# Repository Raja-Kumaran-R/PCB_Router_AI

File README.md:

# KiCad Autorouter with A*

This project implements a simple autorouter for KiCad PCB files using the A* search algorithm.  
It parses `.kicad_pcb` files, generates routes, and injects them back into the PCB design.

## Features
- Parse PCB layout files to extract pads, nets, and obstacles.
- Route nets automatically using A* algorithm.
- Support for via creation between layers.
- Generates new routed KiCad PCB file.

## Current Progress
1. Many sample PCB files are included:
2. Next step: extend support for **4-layer PCBs** and implementing LLM.

## Usage

### Step 1: Parse the PCB File
```bash
python parser.py <file_name>.kicad_pcb
```
This will generate an `input.json` file containing the parsed layout information.

### Step 2: Run A* Routing
```bash
python astar.py input.json > output.json
```
This creates an `output.json` file containing the generated routing paths.

### Step 3: Inject Routes into PCB
```bash
python inject_routes.py output.json <filename>.kicad_pcb <filename>_routed.kicad_pcb
```
This produces a new routed PCB file `<filename>_routed.kicad_pcb`.

### Step 4: Open in KiCad
Open `<filename>_routed.kicad_pcb` in KiCad to check the generated routes.

## Notes
- Works correctly on single-layer boards.
- Vias are being generated and routing is done through vias.
- Currently tested on `Simple_Demo.kicad_pcb`, `Simple_Via.kicad_pcb`, `via2.kicac_pcb` and `via3.kicad_pcb`.(Working perfectly)
- Currently testing on `tht.kicad_pcb`.

## Next Steps
- Improve routing efficiency and optimization.
- Implement LLM.

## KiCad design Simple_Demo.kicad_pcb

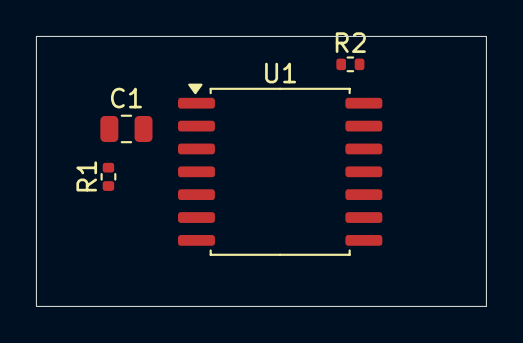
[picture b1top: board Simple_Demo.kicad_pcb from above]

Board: 4 copper layers, 25.0 x 15.0 mm, 4 parts (0 on the bottom side), 5 nets, no tracks yet.

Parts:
C1: C; C_0805_2012Metric
R1, R2: R; R_0402_1005Metric
U1: LM2574HVM-3.3; SOIC-14W_7.5x9mm_P1.27mm

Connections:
GND: C1.2, U1.4 (SGND), U1.6 (PGND)
unnamed: C1.1, R1.2
unnamed: R2.1, U1.3 (FB)
unnamed: R2.2, U1.12 (OUT)
VCC: R1.1, U1.5 (~ON/OFF), U1.10 (VIN)

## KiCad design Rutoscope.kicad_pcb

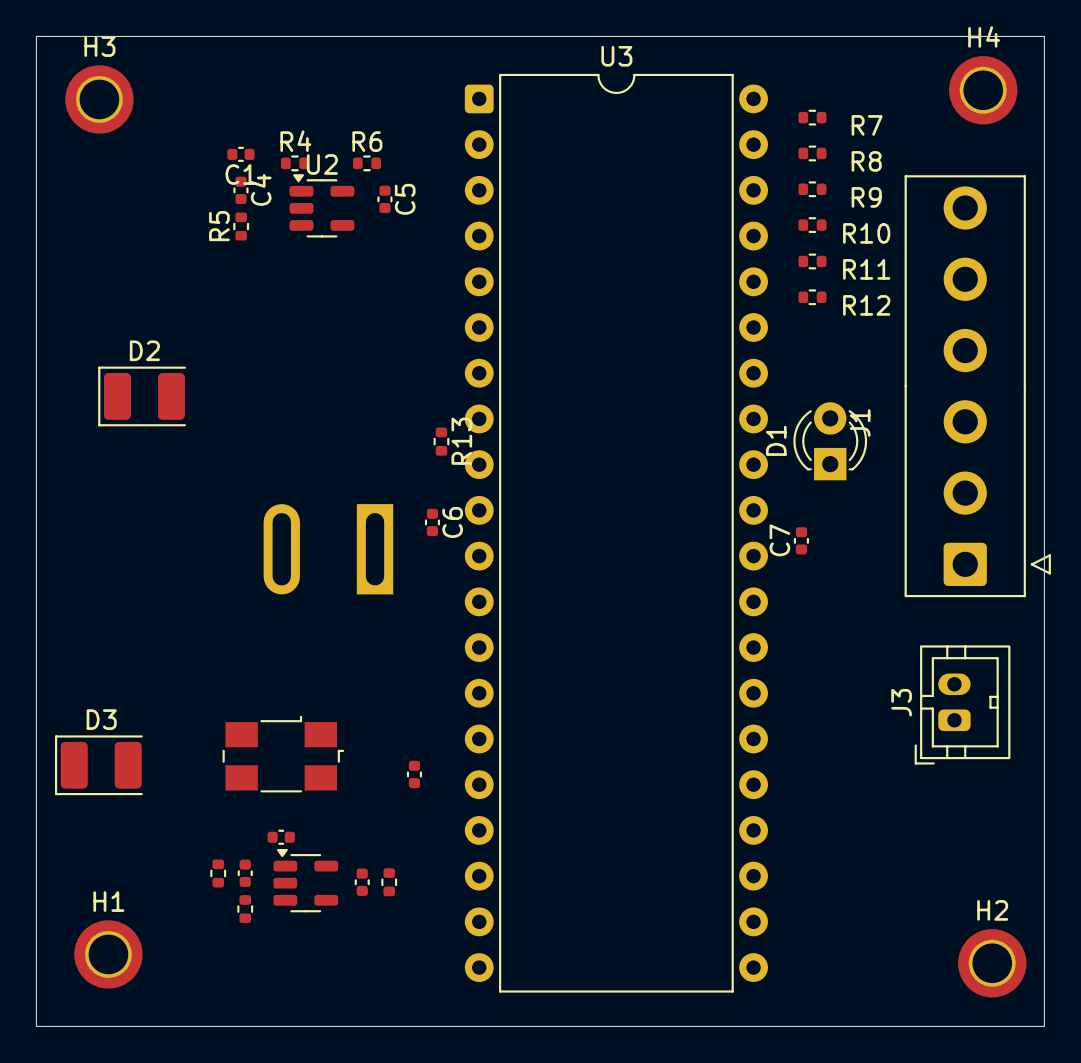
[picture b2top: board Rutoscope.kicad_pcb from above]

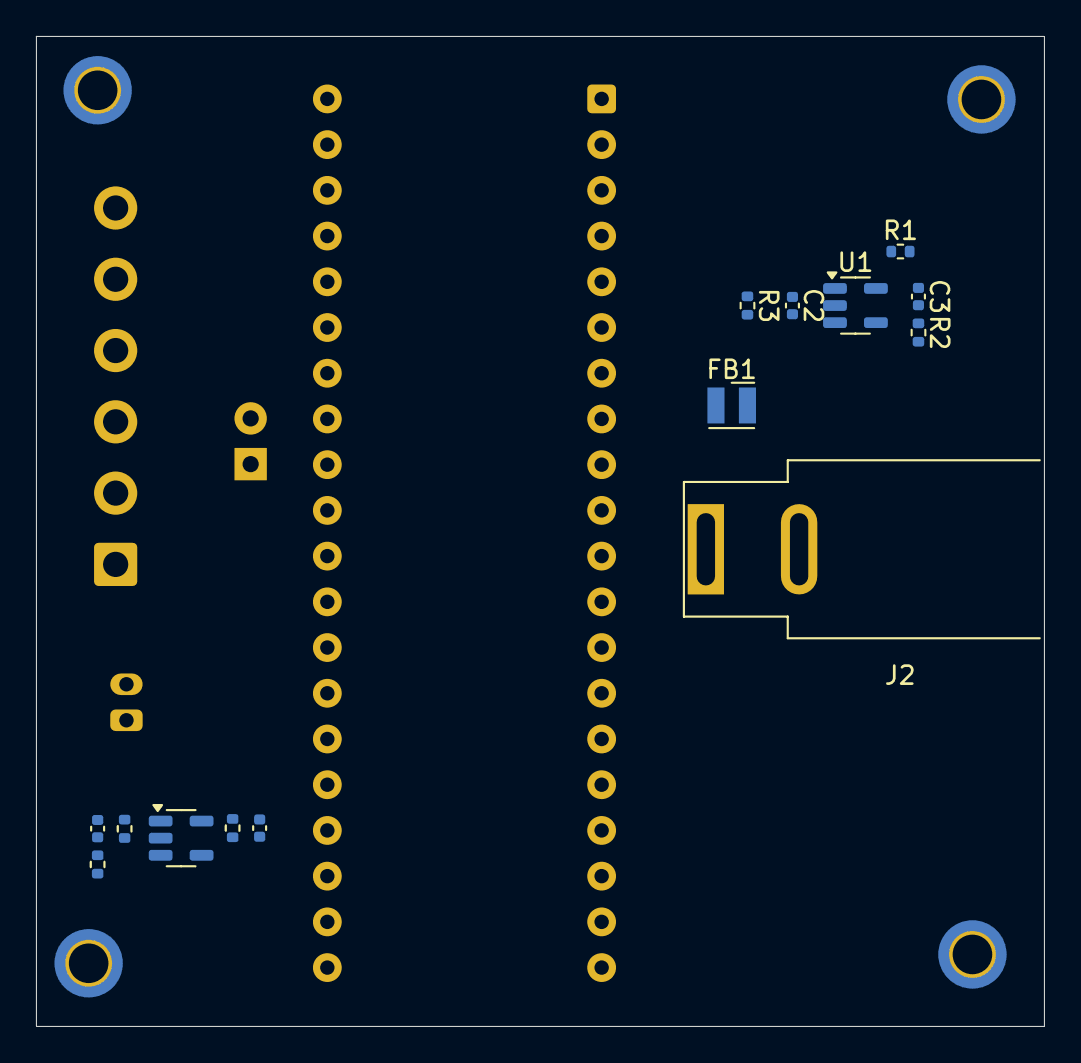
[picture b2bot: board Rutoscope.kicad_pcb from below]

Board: 4 copper layers, 56.0 x 55.0 mm, 49 parts (14 on the bottom side), 26 nets, no tracks yet.

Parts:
C1, C2, C3, C4, C5, C6, C7, C8, C9, C10, C10#2, C11, C11#2: C; C_0402_1005Metric
D1: LED; LED_D3.0mm
D2, D3: LED; LED_PLCC-2_3.4x3.0mm_AK
FB1: FerriteBead; L_Wurth_WE-LQSH-2512
H1, H2, H3, H4: MountingHole; MountingHole_2.2mm_M2_DIN965_Pad_TopBottom
J1: Conn_01x06_Pin; TE_826576-6_1x06_P3.96mm_Vertical
J2: Barrel_Jack; BarrelJack_SwitchcraftConxall_RAPC10U_Horizontal
J3: Conn_01x02_Pin; TE_440054-2_1x02_P2.00mm_Vertical
R1, R2, R3, R4, R5, R6, R7, R8, R9, R10, R11, R12, R13, R14, R14#2, R15, R15#2, R16, R16#2: R; R_0402_1005Metric
U1: MIC5504-3.3YM5; SOT-23-5
U2: MIC5504-1.2YM5; SOT-23-5
U3: ATmega164P-20P; DIP-40_W15.24mm
U4, U4#2: MIC5504-1.8YM5; SOT-23-5
Y1: Crystal_GND24; Crystal_SMD_0603-4Pin_6.0x3.5mm

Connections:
+1V2: C5.1, C6.1, C7.1, D2.2 (A), J3.1, R6.1, U2.5 (VOUT), U3.10 (VCC), U3.30 (AVCC)
+1V8: C11.1, C11#2.1, D3.2 (A), R16.1, R16#2.1, U4.5 (VOUT), U4#2.5 (VOUT)
+3V3: C1.1, C2.1, C4.1, C9.1, C10.1, C10#2.1, R3.1, R4.1, R13.1, R14.1, R14#2.1, U1.5 (VOUT), U2.1 (VIN), U4.1 (VIN), U4#2.1 (VIN)
+5V: C3.1, FB1.2, R1.1, U1.1 (VIN)
GND: C1.2, C2.2, C3.2, C4.2, C5.2, C6.2, C7.2, C9.2, C10.2, C10#2.2, C11.2, C11#2.2, D1.1 (K), D2.1 (K), D3.1 (K), J2.2, R1.2, R2.2, R3.2, R4.2, R5.2, R6.2, R14.2, R14#2.2, R15.2, R15#2.2, R16.2, R16#2.2, U1.2 (GND), U2.2 (GND), U3.11 (GND), U3.31 (GND), U4.2 (GND), U4#2.2 (GND), Y1.2, Y1.4
unnamed: C8.2, Y1.1
unnamed: D1.2 (A), U3.33 (PA7)
unnamed: FB1.1, J2.1
unnamed: J1.1, R12.2
unnamed: J1.2, R11.2
unnamed: J1.3, R10.2
unnamed: J1.4, R9.2
unnamed: J1.5, R8.2
unnamed: J1.6, R7.2
unnamed: J3.2, U3.34 (PA6)
unnamed: R2.1, U1.3 (EN)
unnamed: R5.1, U2.3 (EN)
unnamed: R7.1, U3.40 (PA0)
unnamed: R8.1, U3.39 (PA1)
unnamed: R9.1, U3.38 (PA2)
unnamed: R10.1, U3.37 (PA3)
unnamed: R11.1, U3.36 (PA4)
unnamed: R12.1, U3.35 (PA5)
unnamed: C8.1, U3.13 (XTAL1), Y1.3
unnamed: R13.2, U3.9 (~RESET)
unnamed: R15.1, R15#2.1, U4.3 (EN), U4#2.3 (EN)

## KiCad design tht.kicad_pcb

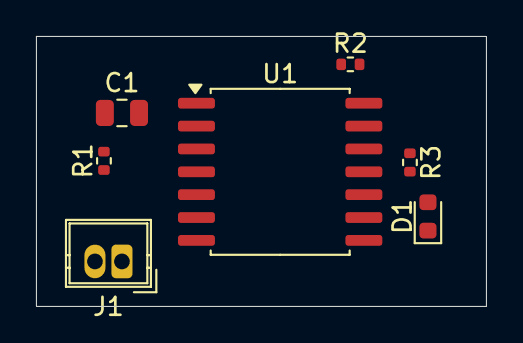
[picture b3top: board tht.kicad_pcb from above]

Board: 4 copper layers, 25.0 x 15.0 mm, 7 parts (0 on the bottom side), 6 nets, no tracks yet.

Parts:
C1: C; C_0805_2012Metric
D1: LED; LED_0603_1608Metric
J1: Conn_01x02_Pin; Wuerth_WR-WTB_64800211622_1x02_P1.50mm_Vertical
R1, R2, R3: R; R_0402_1005Metric
U1: LM2574HVM-3.3; SOIC-14W_7.5x9mm_P1.27mm

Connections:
GND: C1.2, D1.1 (K), J1.1, U1.4 (SGND), U1.6 (PGND)
unnamed: C1.1, R1.2
unnamed: D1.2 (A), R3.2
unnamed: R2.1, U1.3 (FB)
unnamed: R2.2, R3.1, U1.12 (OUT)
VCC: J1.2, R1.1, U1.5 (~ON/OFF), U1.10 (VIN)

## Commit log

2025-11-12 Updated README file
2025-11-14 Moved pcb boards to root folder
2025-11-14 Edited inject_routes.py
